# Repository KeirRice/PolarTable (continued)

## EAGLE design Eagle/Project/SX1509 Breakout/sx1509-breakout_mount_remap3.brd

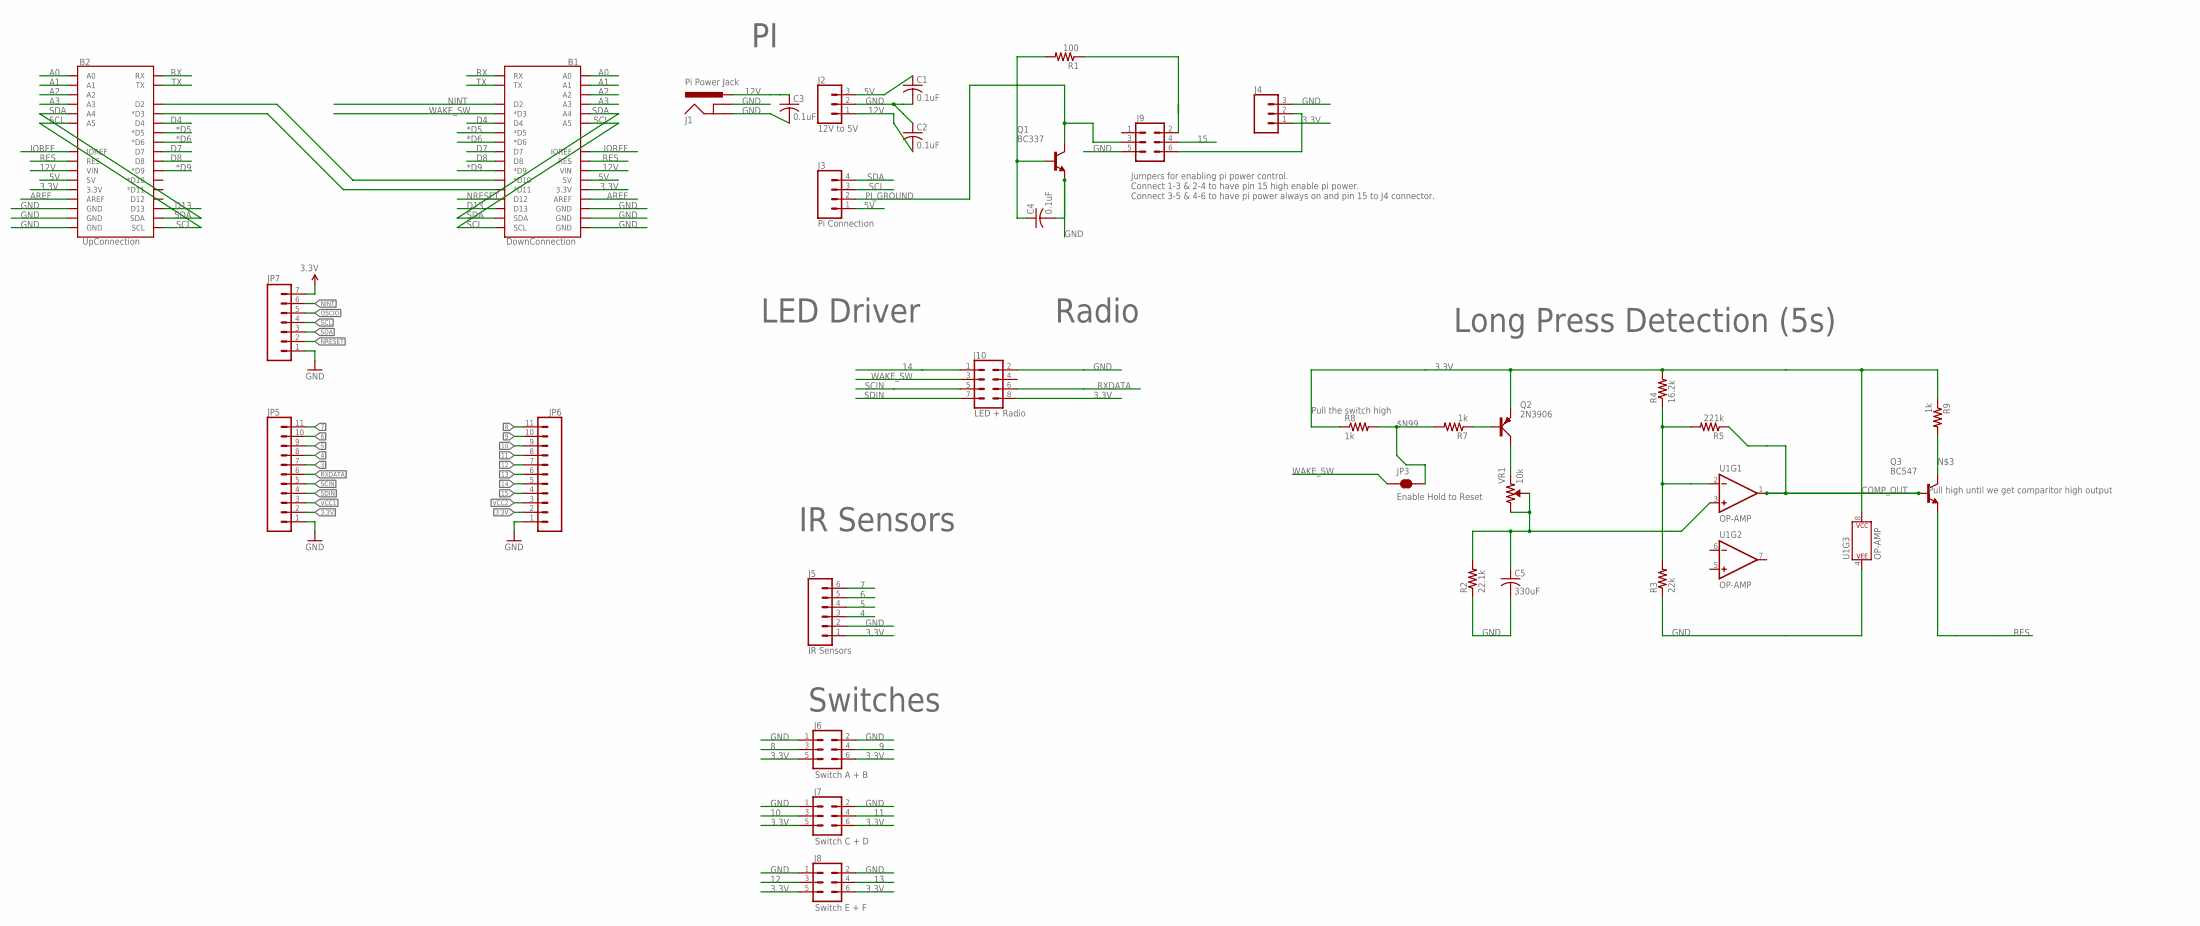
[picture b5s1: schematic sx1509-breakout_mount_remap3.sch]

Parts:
B1: DownConnection; UNO_R3_SHIELD_NOLABELS
B2: UpConnection; UNO_R3_SHIELD_NOLABELS
C1, C2, C3, C4: 0.1uF; C0805
C5: 330uF; C0805
J1: Pi Power Jack; POWER_JACK_PTH_BREAD
J2: 12V to 5V; 1X03
J3: Pi Connection; 1X04
J4: CONN_03; 1X03
J5: IR Sensors; 1X06
J6: Switch A + B; 2X3
J7: Switch C + D; 2X3
J8: Switch E + F; 2X3
J9: CONN_03X2NO_SILK; 2X3-NS
J10: LED + Radio; 2X4
JP3: Enable Hold to Reset; SMT-JUMPER_2_NC_TRACE_SILK
JP5, JP6: CONN_11; 1X11
JP7: M07; 1X07
Q1: BC337; TO92
Q2: 2N3906; TO92D
Q3: BC547; TO92
R1: 100; R0805
R2: 22.1k; R0805
R3: 22k; R0805
R4: 16.2k; R0805
R5: 221k; R0805
R7, R8, R9: 1k; R0805
U1: OP-AMP; SO08
VR1: 10k; TRIMPOT-PTH-3386U

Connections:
3: JP5.7
3.3V: B1.3.3V, B2.3.3V, J4.1, J5.1, J6.5, J6.6, J7.5, J7.6, J8.5, J8.6, J10.8, JP5.2, JP6.2, JP7.7, Q2.E, R4.2, R8.1, R9.1, U1.8 (P$V+)
4: J5.3, JP5.8
5: J5.4, JP5.9
5V: B1.5V, B2.5V, C1.1, J2.3, J3.1
6: J5.5, JP5.10
7: J5.6, JP5.11
8: J6.3, JP6.11
9: J6.4, JP6.10
10: J7.3, JP6.9
10_TO_2: B1.D10 (*D10), B2.D2
11: J7.4, JP6.8
11_TO_3: B1.D11 (*D11), B2.D3 (*D3)
12: J8.3, JP6.7
12V: B1.VIN, B2.VIN, C2.2, C3.1, J1.PWR, J2.1
13: J8.4, JP6.6
14: J10.1, JP6.5
15: J9.4, JP6.4
15_PLUG: J4.2, J9.6
$N99: JP3.2, R7.2, R8.2
*D5: B1.D5 (*D5), B2.D5 (*D5)
*D6: B1.D6 (*D6), B2.D6 (*D6)
*D9: B1.D9 (*D9), B2.D9 (*D9)
A0: B1.A0, B2.A0
A1: B1.A1, B2.A1
A2: B1.A2, B2.A2
A3: B1.A3, B2.A3
AREF: B1.AREF, B2.AREF
COMP_OUT: Q3.2 (B), R5.1, U1.1 (OUT)
D4: B1.D4, B2.D4
D7: B1.D7, B2.D7
D8: B1.D8, B2.D8
D13: B1.D13, B2.D13
GND: B1.GND@0 (GND), B1.GND@1 (GND), B1.GND@2 (GND), B2.GND@0 (GND), B2.GND@1 (GND), B2.GND@2 (GND), C1.2, C2.1, C3.2, C4.2, C5.2, J1.GND, J1.GNDBREAK, J2.2, J4.3, J5.2, J6.1, J6.2, J7.1, J7.2, J8.1, J8.2, J9.5, J10.2, JP5.1, JP6.1, JP7.1, Q1.1 (E), R2.1, R3.1, U1.4 (P$V-)
IOREF: B1.IOREF, B2.IOREF
unnamed: Q2.B, R7.1
unnamed: C4.1, Q1.2 (B), R1.2
unnamed: Q3.3 (C), R9.2
unnamed: J9.2, R1.1
unnamed: R3.2, R4.1, R5.2, U1.2 (-IN)
unnamed: Q2.C, VR1.1 (CCW)
unnamed: C5.1, R2.2, U1.3 (+IN), VR1.2 (WIPER), VR1.3 (CW)
NINT: B1.D2, JP7.6
NRESET: B1.D12, JP7.2
OSCIO: JP7.5
PI_GROUND: J3.2, J9.3, Q1.3 (C)
RES: B1.RES, B2.RES, Q3.1 (E)
RX: B1.RX, B2.RX
RXDATA: J10.6, JP5.6
SCIN: J10.5, JP5.5
SCL: B1.A5, B1.SCL, B2.A5, B2.SCL, J3.3, JP7.4
SDA: B1.A4, B1.SDA, B2.A4, B2.SDA, J3.4, JP7.3
SDIN: J10.7, JP5.4
TX: B1.TX, B2.TX
VCC1: JP5.3
VCC2: JP6.3
WAKE_SW: B1.D3 (*D3), J10.3, JP3.1

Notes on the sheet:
LED Driver
IR Sensors
Switches
Radio
Long Press Detection (5s)
Jumpers for enabling pi power control. Connect 1-3 & 2-4 to have pin 15 high enable pi power. Connect 3-5 & 4-6 to have pi power always on and pin 15 to J4 connector.

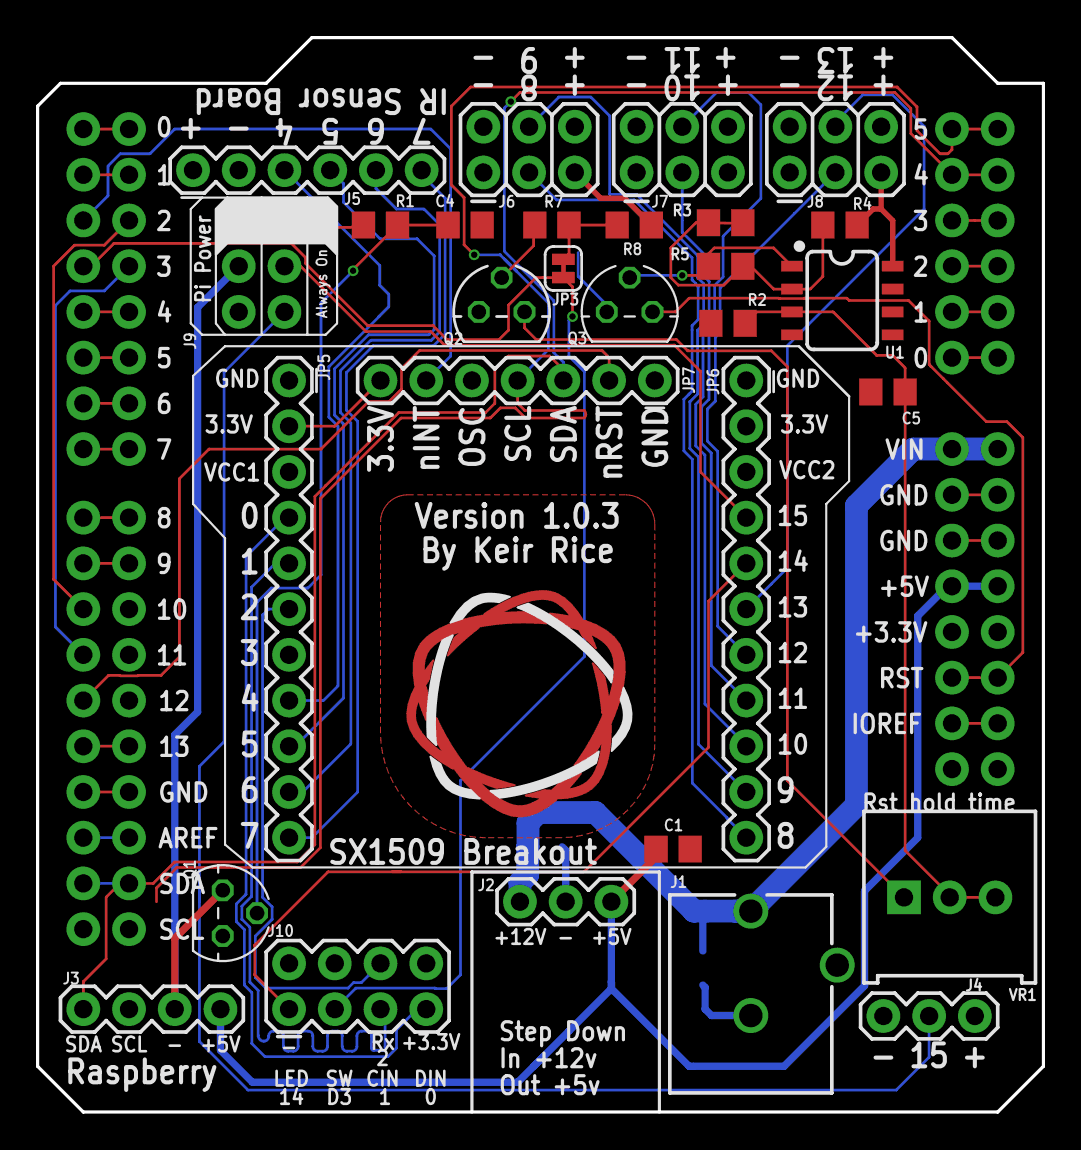
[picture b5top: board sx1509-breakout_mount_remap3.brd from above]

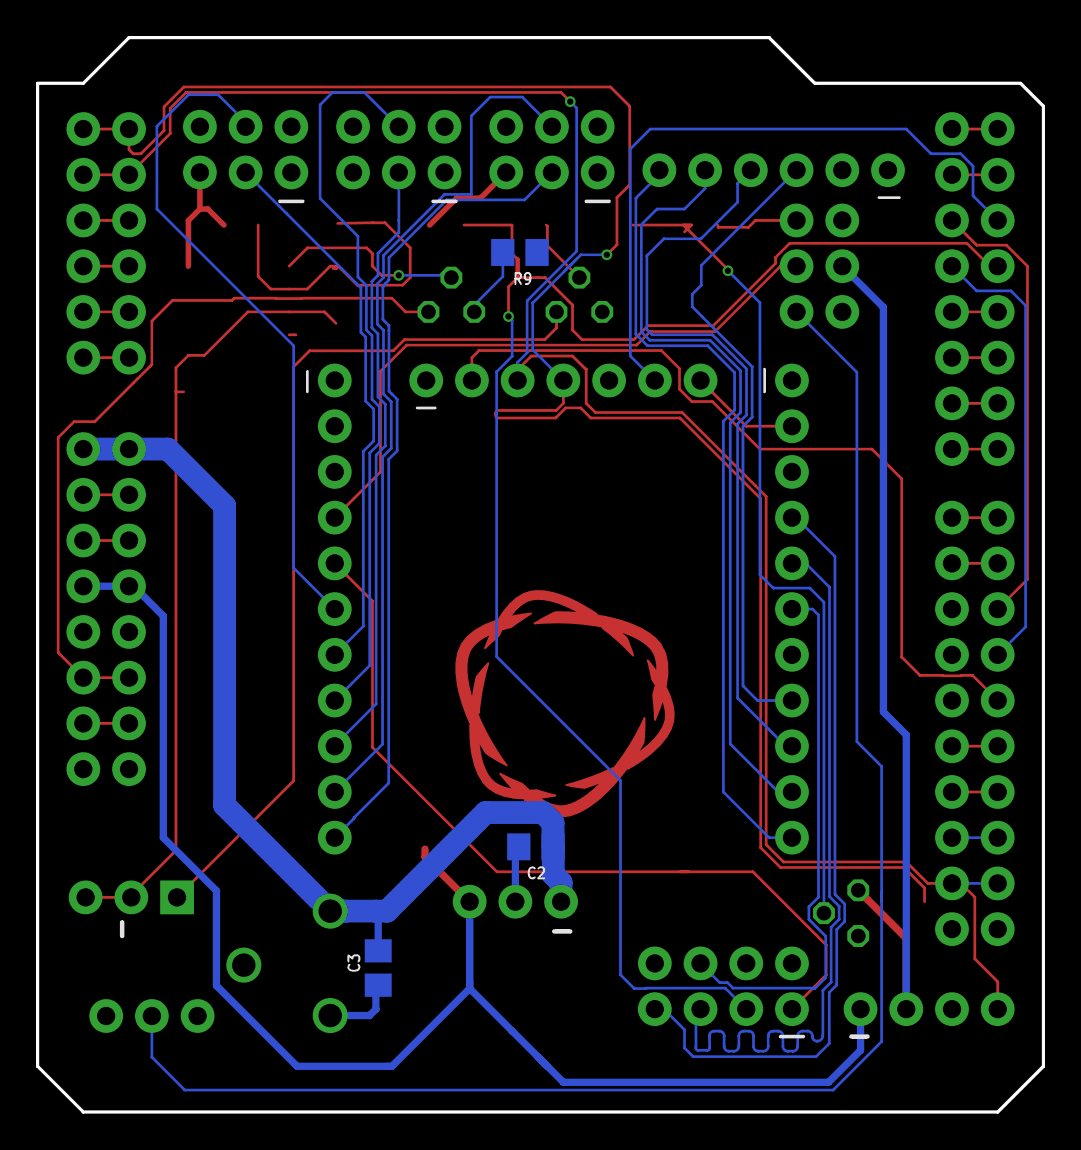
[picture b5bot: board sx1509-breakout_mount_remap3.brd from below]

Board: 2 copper layers, 55.9 x 59.7 mm, 35 parts (3 on the bottom side), 53 nets.

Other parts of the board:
U$2: TRI_LOGO_TOP_15MM

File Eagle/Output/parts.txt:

Partlist

Exported from sx1509-breakout_mount_remap5.sch at 9/27/2018 1:54 PM

EAGLE Version 9.1.3 Copyright (c) 1988-2018 Autodesk, Inc.

Assembly variant: 

Part     Value                         Device                         Package                      Library                 Sheet

B1       Connect down to Arduino       ARDUINO_UNO_R3_SHIELDNOLABELS  UNO_R3_SHIELD_NOLABELS       keir_library            1
B2       Connect up to motor shield    ARDUINO_UNO_R3_SHIELDNOLABELS  UNO_R3_SHIELD_NOLABELS       keir_library            1
C1       100u                          CPOL-EUE2-5                    E2-5                         rcl                     1
C2       100u                          CPOL-EUE2-5                    E2-5                         rcl                     1
C4       100nF                         C-EUC0805                      C0805                        resistor                1
C5       330uF                         C-EUC0805                      C0805                        resistor                1
C9       100n                          C-EUC0805                      C0805                        rcl                     1
D1       1N5408                        1N5408                         DO15-12                      keir_library            1
IC2      LM358D                        LM358D                         SO08                         keir_library            1
J1       Pi Power Jack                 POWER_JACKPTH_BREAD            POWER_JACK_PTH_BREAD         SparkFun-Connectors     1
J2       Header - Right angled, female CONN_031X03_2.54MM_RA_FEMALE   1X03                         keir_library            1
J3       Pi Connection                 CONN_041X04_1.24MM_RA_MALE     1X04_1.24MM_RA_MALE          keir_library            1
J4                                     CONN_041X04_1.24MM_RA_MALE     1X04_1.24MM_RA_MALE          keir_library            1
J5       IR Sensors                    CONN_06SILK_FEMALE_PTH         1X06                         SparkFun-Connectors     1
J6       Switch A + B                  CONN_03X22X03_2.54MM_RA_MALE   2X3                          keir_library            1
J7       Switch C + D                  CONN_03X22X03_2.54MM_RA_MALE   2X3                          keir_library            1
J8       Switch E + F                  CONN_03X22X03_2.54MM_RA_MALE   2X3                          keir_library            1
J10      LED + Radio                   CONN_04X22X4_1.24MM_RA_MALE    2X4                          keir_library            1
JP2      Bypass Power Control          JUMPER-SMT_2_NO_SILK_ROUND     SMT-JUMPER_2_NO_SILK_ROUND   SparkFun-Jumpers        1
JP3      Enable Hold to Reset          JUMPER-SMT_2_NC_TRACE_SILK     SMT-JUMPER_2_NC_TRACE_SILK   SparkFun-Jumpers        1
JP4      Route 15 to external          JUMPER-SMT_3_1-NC_TRACE_SILK   SMT-JUMPER_3_1-NC_TRACE_SILK SparkFun-Jumpers        1
JP5                                    CONN_11                        1X11                         SparkFun-Connectors     1
JP6                                    CONN_11                        1X11                         SparkFun-Connectors     1
JP7                                    M07                            1X07                         SparkFun-Connectors     1
Q1       BC337                         BC337                          TO92                         transistor-npn          1
Q2       2N3906                        2N3906                         TO92D                        transistor-small-signal 1
Q3       BC547                         BC547                          TO92                         transistor-npn          1
R1       100                           R-US_R0805                     R0805                        resistor                1
R2       22.1k                         R-US_R0805                     R0805                        resistor                1
R3       22k                           R-US_R0805                     R0805                        resistor                1
R4       16.2k                         R-US_R0805                     R0805                        resistor                1
R5       221k                          R-US_R0805                     R0805                        resistor                1
R7       1k                            R-US_R0805                     R0805                        resistor                1
R8       1k                            R-US_R0805                     R0805                        resistor                1
R9       1k                            R-US_R0805                     R0805                        resistor                1
U3       SN74HC595DR                   SN74HC595HCD                   SO16                         keir_library            1
VR1      10k                           TRIMPOT-PTH-10MM-KNOB-1/2W-10% TRIMPOT-PTH-3386U            SparkFun-Resistors      1

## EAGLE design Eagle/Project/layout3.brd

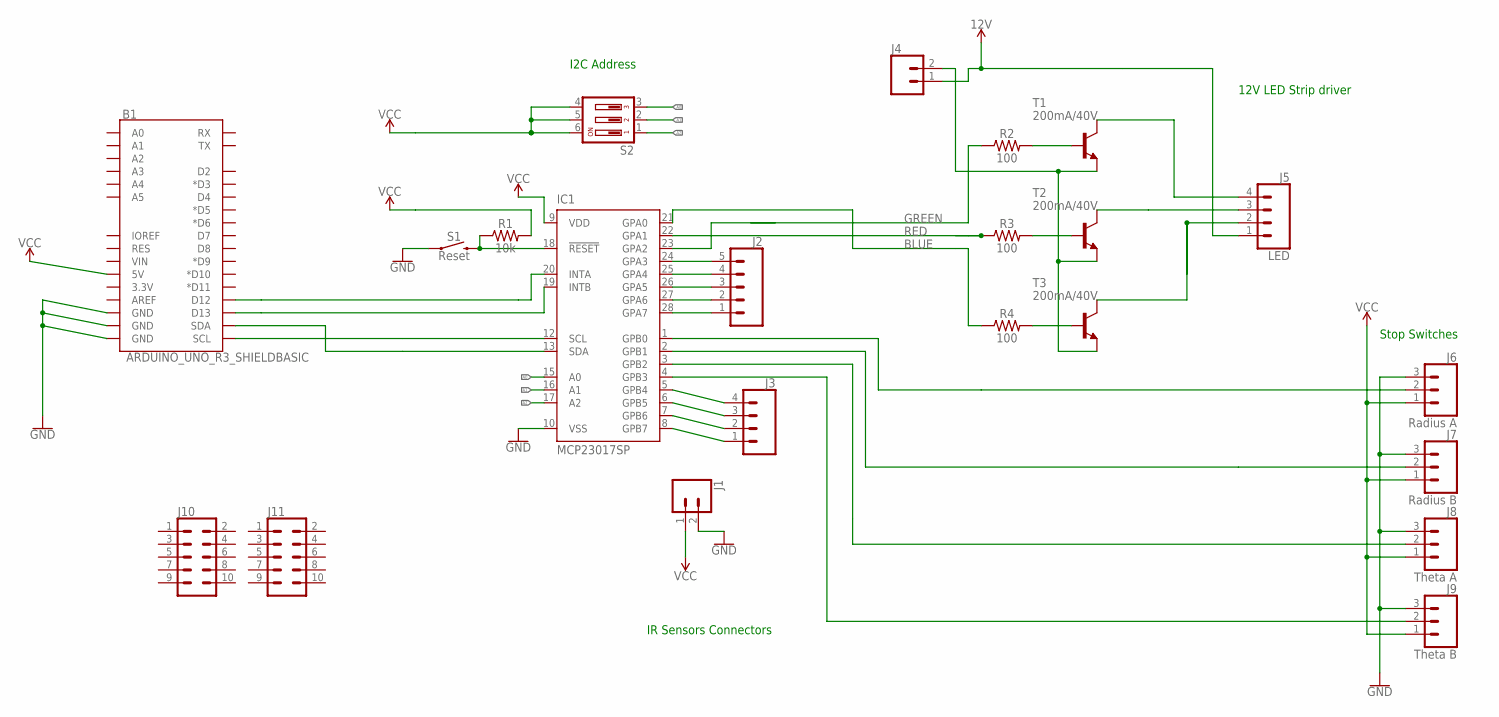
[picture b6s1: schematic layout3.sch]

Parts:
B1: ARDUINO_UNO_R3_SHIELDBASIC; UNO_R3_SHIELD
IC1: MCP23017SP; DIL28-3
J1: CONN_02POLAR; MOLEX-1X2
J2: CONN_05; 1X05
J3: CONN_041.27MM; 1X04_1.27MM
J4: CONN_023.5MM; SCREWTERMINAL-3.5MM-2
J5: LED; MOLEX-1X4
J6: Radius A; MOLEX-1X3
J7: Radius B; MOLEX-1X3
J8: Theta A; MOLEX-1X3
J9: Theta B; MOLEX-1X3
J10, J11: CONN_05X2NO_SILK; 2X5_NOSILK
R1: 10k; 0603
R2, R3, R4: 100; 0603
S1: Reset; TACTILE_SWITCH_PTH_6.0MM
S2: DS03; DS-03
T1, T2, T3: 200mA/40V; TO220

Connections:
12V: J4.1, J5.1
A0: IC1.15 (A0), S2.3
A1: IC1.16 (A1), S2.2
A2: IC1.17 (A2), S2.1
BLUE: IC1.21 (GPA0), R4.1
GND: B1.GND@0 (GND), B1.GND@1 (GND), B1.GND@2 (GND), IC1.10 (VSS), J1.2, J6.3, J7.3, J8.3, J9.3, S1.1
GREEN: IC1.23 (GPA2), R2.1
INT_A: B1.D12, IC1.20 (INTA)
INT_B: B1.D13, IC1.19 (INTB)
IR_A: IC1.5 (GPB4), J3.4
IR_B: IC1.6 (GPB5), J3.3
IR_C: IC1.7 (GPB6), J3.2
IR_D: IC1.8 (GPB7), J3.1
unnamed: R2.2, T1.1 (B)
unnamed: J5.4, T1.2 (C)
unnamed: R3.2, T2.1 (B)
unnamed: J5.3, T2.2 (C)
unnamed: R4.2, T3.1 (B)
unnamed: J5.2, T3.2 (C)
unnamed: J4.2, T1.3 (E), T2.3 (E), T3.3 (E)
unnamed: IC1.28 (GPA7), J2.1
unnamed: IC1.27 (GPA6), J2.2
unnamed: IC1.26 (GPA5), J2.3
unnamed: IC1.25 (GPA4), J2.4
unnamed: IC1.24 (GPA3), J2.5
RADIUS_A: IC1.1 (GPB0), J6.2
RADIUS_B: IC1.2 (GPB1), J7.2
RED: IC1.22 (GPA1), R3.1
RESET: IC1.18 (!RESET), R1.1, S1.3 (2)
SDA: B1.SDA, IC1.13 (SDA)
SDL: B1.SCL, IC1.12 (SCL)
THETA_A: IC1.3 (GPB2), J8.2
THETA_B: IC1.4 (GPB3), J9.2
VCC: B1.5V, IC1.9 (VDD), J1.1, J6.1, J7.1, J8.1, J9.1, R1.2, S2.4, S2.5, S2.6

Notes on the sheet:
Stop Switches
12V LED Strip driver
I2C Address
IR Sensors Connectors

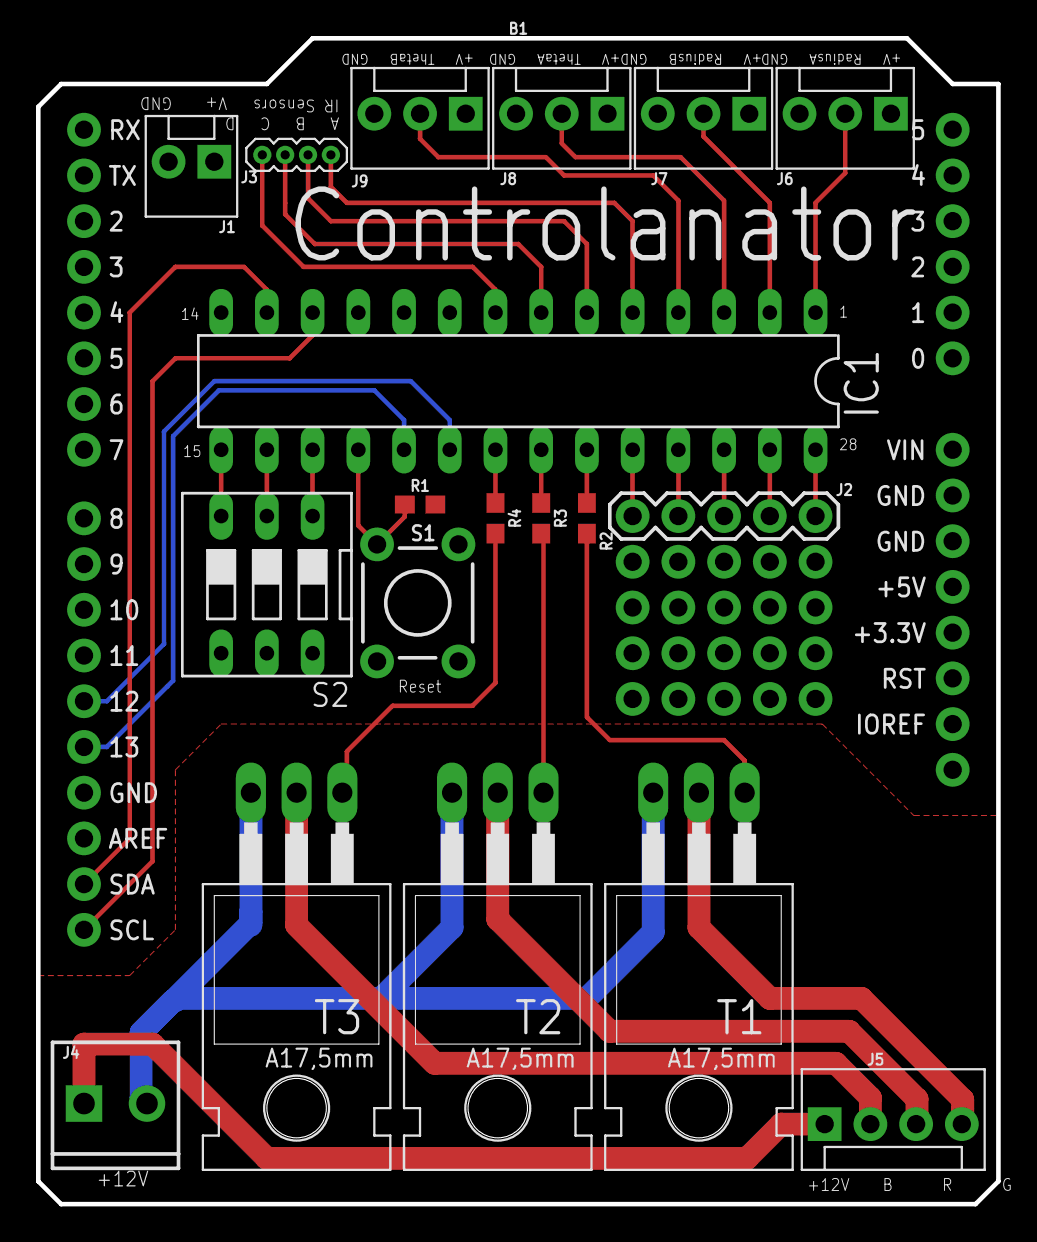
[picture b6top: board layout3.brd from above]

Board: 2 copper layers, 53.3 x 64.8 mm, 22 parts (0 on the bottom side), 34 nets.

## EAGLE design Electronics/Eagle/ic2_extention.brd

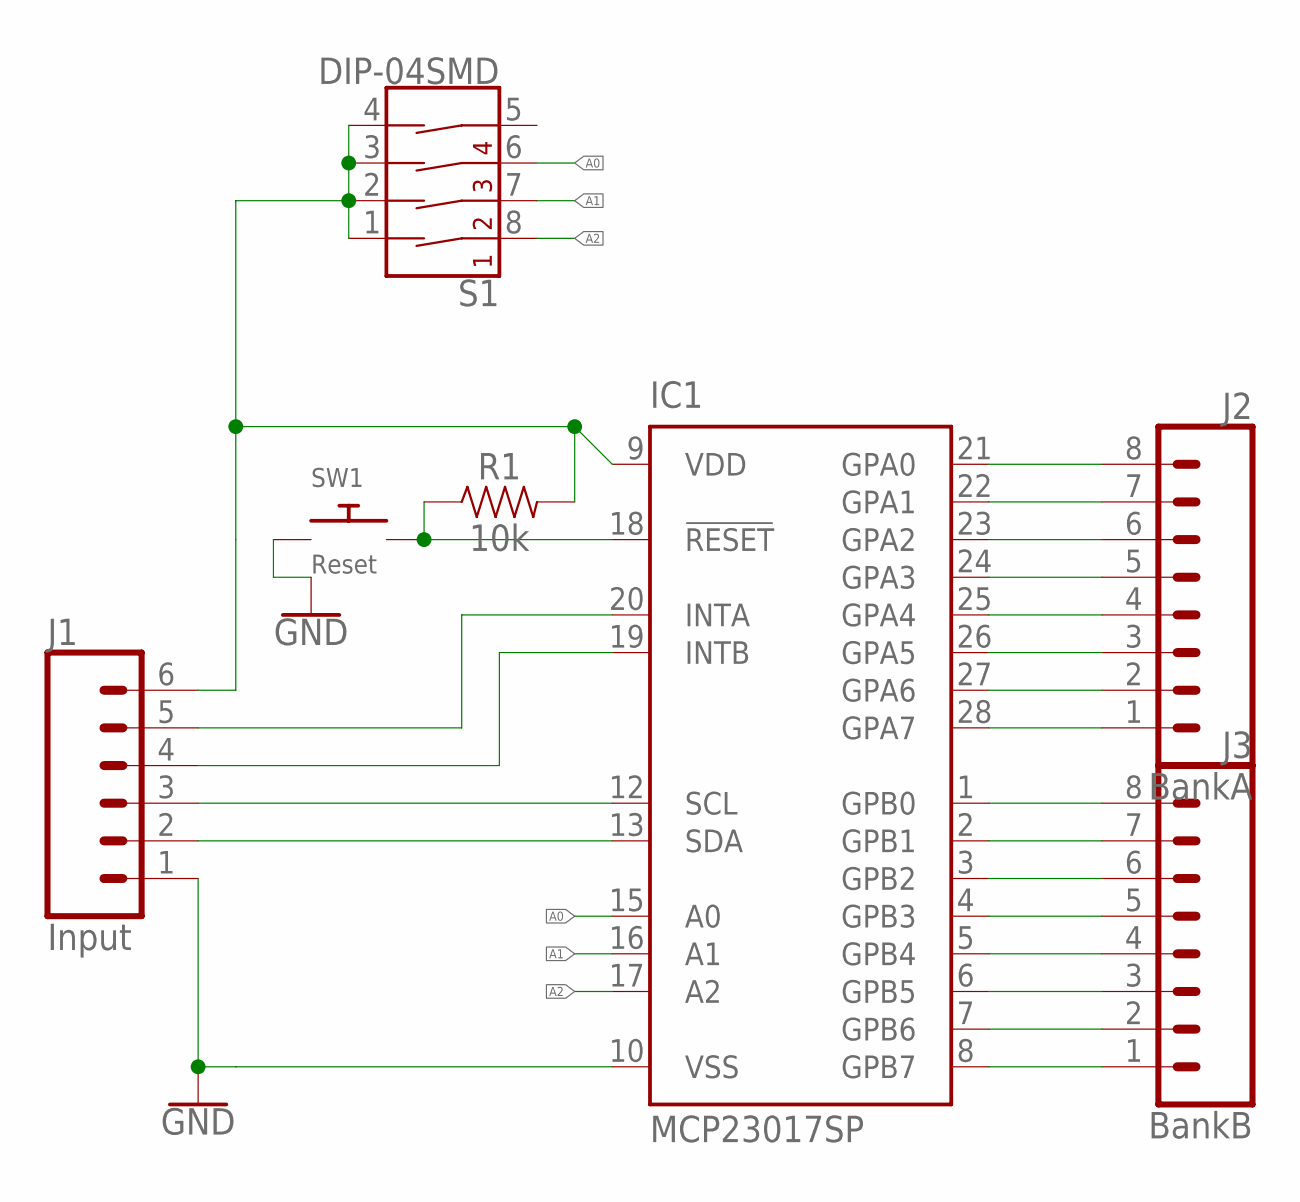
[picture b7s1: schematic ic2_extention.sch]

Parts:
IC1: MCP23017SP; DIL28-3
J1: Input; 1X06_LOCK
J2: BankA; 1X08
J3: BankB; 1X08
R1: 10k; 0603
S1: DIP-04SMD; DIPSWITCH-04-SMD
SW1: Reset; BTN_CK_KSS

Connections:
A0: IC1.15 (A0), S1.6 (3B)
A1: IC1.16 (A1), S1.7 (2B)
A2: IC1.17 (A2), S1.8 (1B)
GND: IC1.10 (VSS), J1.1, SW1.P$1
unnamed: IC1.18 (!RESET), R1.1, SW1.P$2
unnamed: IC1.20 (INTA), J1.5
unnamed: IC1.19 (INTB), J1.4
unnamed: IC1.28 (GPA7), J2.1
unnamed: IC1.27 (GPA6), J2.2
unnamed: IC1.26 (GPA5), J2.3
unnamed: IC1.25 (GPA4), J2.4
unnamed: IC1.24 (GPA3), J2.5
unnamed: IC1.23 (GPA2), J2.6
unnamed: IC1.22 (GPA1), J2.7
unnamed: IC1.21 (GPA0), J2.8
unnamed: IC1.8 (GPB7), J3.1
unnamed: IC1.7 (GPB6), J3.2
unnamed: IC1.6 (GPB5), J3.3
unnamed: IC1.5 (GPB4), J3.4
unnamed: IC1.4 (GPB3), J3.5
unnamed: IC1.3 (GPB2), J3.6
unnamed: IC1.2 (GPB1), J3.7
unnamed: IC1.1 (GPB0), J3.8
unnamed: IC1.12 (SCL), J1.3
unnamed: IC1.13 (SDA), J1.2
VDD: IC1.9 (VDD), J1.6, R1.2, S1.1 (1A), S1.2 (2A), S1.3 (3A), S1.4 (4A)

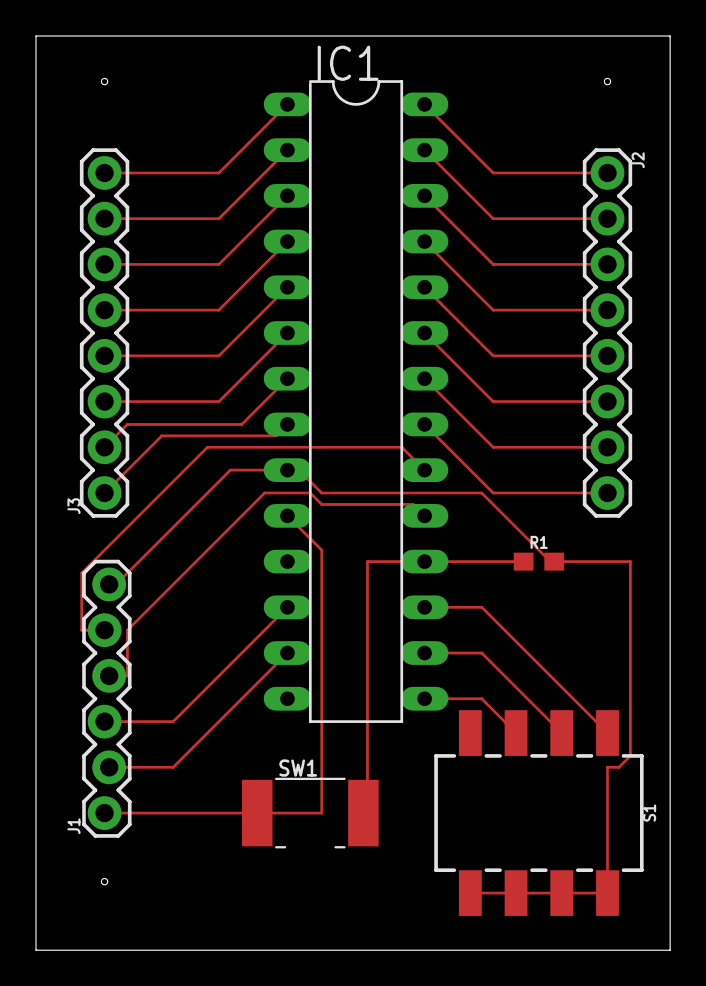
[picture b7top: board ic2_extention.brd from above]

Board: 2 copper layers, 35.2 x 50.8 mm, 7 parts (0 on the bottom side), 26 nets.

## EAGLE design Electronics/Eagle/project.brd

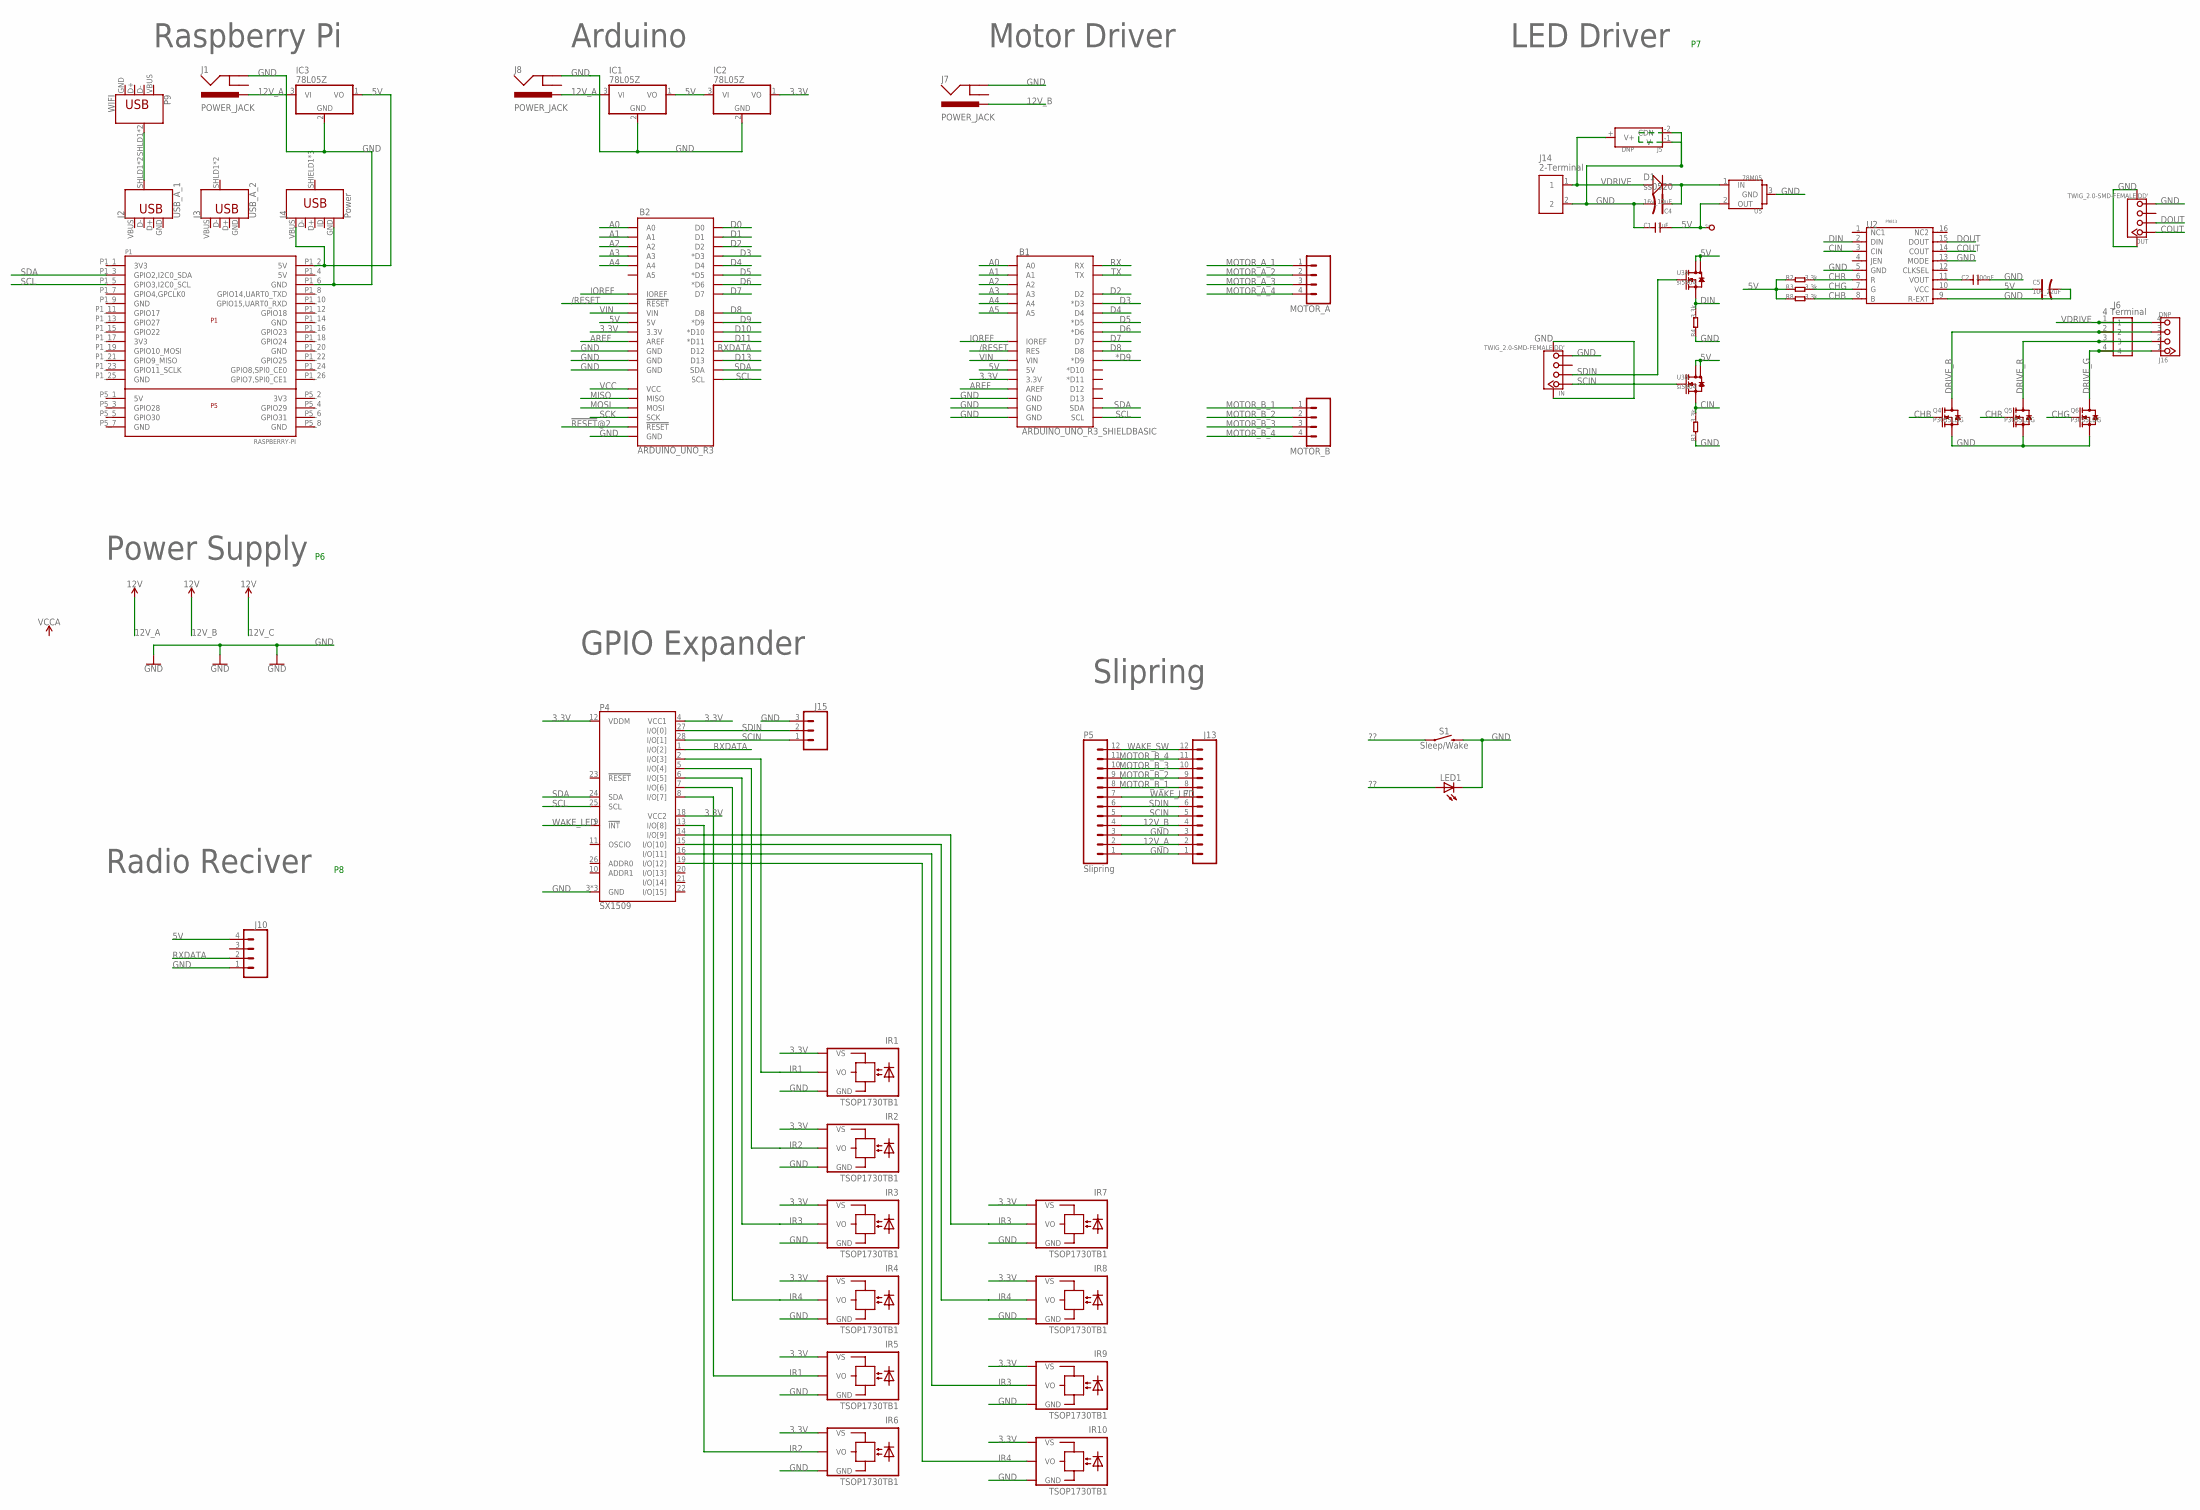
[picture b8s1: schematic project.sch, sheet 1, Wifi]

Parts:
5V: DNP; TP_3535
B1: ARDUINO_UNO_R3_SHIELDBASIC; UNO_R3_SHIELD
B2: ARDUINO_UNO_R3; ARDUINO_R3
C1: 1uF; 0805
C2: 100nF; 0402
C4: 16v_10uF; AVX-A
C5: 10v_22uF; AVX-A
D1: ss0520; SOD123
IC1, IC2, IC3: 78L05Z; TO92
IN: TWIG_2.0-SMD-FEMALE'DD'; 2.0_1X4DD
IR1, IR2, IR3, IR4, IR5, IR6, IR7, IR8, IR9, IR10: TSOP1730TB1; TSOP17_TB1
J1, J7, J8: POWER_JACK; POWER_JACK_PTH
J2: USB_A_1; USB-A-S-SILK-FEMALE
J3: USB_A_2; USB-A-S-SILK-FEMALE
J4: Power; USB-B-MICRO-SMD
J5: DNP; PW-3P-2.5
J6: 4 Terminal; 4P-2.54-15.6X12.2X13.2
J10: CONN_04; 1X04
J13: CONN_12; 1X12
J14: 2-Terminal; 2P-2.54-12.1X8.5X13.4
J15: CONN_03; 1X03
J16: DNP; 4P-2.54-90
LED1: LED5MM
MOTOR_A: CONN_04SCREW; SCREWTERMINAL-3.5MM-4
MOTOR_B: CONN_04SCREW; SCREWTERMINAL-3.5MM-4
OUT: TWIG_2.0-SMD-FEMALE'DD'; 2.0_1X4DD
P1: RASPBERRY-PI; RASPBERRY-PI_REV2
P4: SX1509; QFN-28
P5: Slipring; 1X12
P9: WIFI; USB-A-H
Q4, Q5, Q6: P3055LDG; TO252
R1, R2, R3, R4, R8: 3.3k; 0402
S1: Sleep/Wake; TACTILE_SWITCH_PTH_6.0MM
U2: P9813; SSOP16
U3: si5904; 1206-8
U5: 78M05; TO252

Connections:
3.3V: B1.3.3V, B2.3.3V, IC2.1 (VO), IR1.VS, IR2.VS, IR3.VS, IR4.VS, IR5.VS, IR6.VS, IR7.VS, IR8.VS, IR9.VS, IR10.VS, P4.4 (VCC1), P4.12 (VDDM), P4.18 (VCC2)
5V: 5V.T, B1.5V, B2.5V, C1.2, C5.+, IC1.1 (VO), IC2.3 (VI), IC3.1 (VO), J4.VBUS, J10.4, P1.P1_2 (5V), R2.1, R3.1, R8.1, U2.10 (VCC), U3.5 (D), U3.6 (D), U3.7 (D), U3.8 (D), U5.2 (OUT)
12V_A: IC1.3 (VI), IC3.3 (VI), J1.PWR, J8.PWR, J13.2, P5.2
12V_B: J7.PWR, J13.4, P5.4
!RESET!@2: B2.RESET@2 (!RESET!)
*D9: B1.D9 (*D9)
/RESET: B1.RES, B2.RESET@1 (!RESET!)
??: LED1.A, S1.1
A0: B1.A0, B2.A0
A1: B1.A1, B2.A1
A2: B1.A2, B2.A2
A3: B1.A3, B2.A3
A4: B1.A4, B2.A4
A5: B1.A5
AREF: B1.AREF, B2.AREF
CHB: Q4.1 (G), R8.2, U2.8 (B)
CHG: Q6.1 (G), R3.2, U2.7 (G)
CHR: Q5.1 (G), R2.2, U2.6 (R)
CIN: R1.2, U2.3 (CIN), U3.3 (S)
COUT: OUT.1, U2.14 (COUT)
D0: B2.D0
D1: B2.D1
D2: B1.D2, B2.D2
D3: B1.D3 (*D3), B2.D3 (*D3)
D4: B1.D4, B2.D4
D5: B1.D5 (*D5), B2.D5 (*D5)
D6: B1.D6 (*D6), B2.D6 (*D6)
D7: B1.D7, B2.D7
D8: B1.D8, B2.D8
D9: B2.D9 (*D9)
D10: B2.D10 (*D10)
D11: B2.D11 (*D11)
D13: B2.D13
DIN: R4.2, U2.2 (DIN), U3.1 (S)
DOUT: OUT.2, U2.15 (DOUT)
DRIVE_B: J6.2, J16.3, Q4.2 (D)
DRIVE_G: J6.4, J16.1, Q6.2 (D)
DRIVE_R: J6.3, J16.2, Q5.2 (D)
GND: B1.GND@0 (GND), B1.GND@1 (GND), B1.GND@2 (GND), B2.GND@1 (GND), B2.GND@2 (GND), B2.GND@3 (GND), B2.GND@4 (GND), C1.1, C2.2, C4.-, C5.-, IC1.2 (GND), IC2.2 (GND), IC3.2 (GND), IN.4, IN.SS1, IN.SS2, IR1.GND, IR2.GND, IR3.GND, IR4.GND, IR5.GND, IR6.GND, IR7.GND, IR8.GND, IR9.GND, IR10.GND, J1.GND, J2.GND, J3.GND, J4.GND, J5.-1 (V-), J5.-2 (CDN), J7.GND, J8.GND, J10.1, J13.1, J13.3, J14.2, J15.3, LED1.K (C), OUT.4, OUT.SS1, OUT.SS2, P1.P1_6 (GND), P4.3 (GND), P4.17 (GND), P4.29 (GND), P5.1, P5.3, P9.GND, Q4.3 (S), Q5.3 (S), Q6.3 (S), R1.1, R4.1, S1.3 (2), U2.5 (GND), U2.9 (R-EXT), U2.13 (MODE), U5.3 (GND)
IOREF: B1.IOREF, B2.IOREF
IR1: IR1.VO, IR5.VO, P4.2 (I/O[3]), P4.8 (I/O[7])
IR2: IR2.VO, IR6.VO, P4.5 (I/O[4]), P4.13 (I/O[8])
IR3: IR3.VO, IR7.VO, IR9.VO, P4.6 (I/O[5]), P4.14 (I/O[9]), P4.16 (I/O[11])
IR4: IR4.VO, IR8.VO, IR10.VO, P4.7 (I/O[6]), P4.15 (I/O[10]), P4.19 (I/O[12])
MISO: B2.MISO
MOSI: B2.MOSI
MOTOR_A_1: MOTOR_A.1
MOTOR_A_2: MOTOR_A.2
MOTOR_A_3: MOTOR_A.3
MOTOR_A_4: MOTOR_A.4
MOTOR_B_1: J13.8, MOTOR_B.1, P5.8
MOTOR_B_2: J13.9, MOTOR_B.2, P5.9
MOTOR_B_3: J13.10, MOTOR_B.3, P5.10
MOTOR_B_4: J13.11, MOTOR_B.4, P5.11
unnamed: J2.SHLD1 (SHIELD), J2.SHLD2 (SHIELD), P9.SHLD1 (SHIELD), P9.SHLD2 (SHIELD)
unnamed: C2.1, U2.11 (VOUT)
unnamed: C4.+, D1.-, U5.1 (IN)
RX: B1.RX
RXDATA: B2.D12, J10.2, P4.1 (I/O[2])
SCIN: IN.1, J13.5, J15.1, P4.28 (I/O[1]), P5.5, U3.4 (G)
SCK: B2.SCK
SCL: B1.SCL, B2.SCL, P1.P1_5 (GPIO3,I2C0_SCL), P4.25 (SCL)
SDA: B1.SDA, B2.SDA, P1.P1_3 (GPIO2,I2C0_SDA), P4.24 (SDA)
SDIN: IN.2, J13.6, J15.2, P4.27 (I/O[0]), P5.6, U3.2 (G)
TX: B1.TX
VBUS: J2.VBUS, J3.VBUS, P9.VBUS
VCC: B2.VCC
VDRIVE: D1.+, J5.+ (V+), J6.1, J14.1, J16.4
VIN: B1.VIN, B2.VIN
WAKE_LED: J13.7, P4.9 (!INT), P5.7
WAKE_SW: J13.12, P5.12

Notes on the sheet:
Arduino
Motor Driver
Power Supply
Raspberry Pi
LED Driver
GPIO Expander
Slipring
Radio Reciver

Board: 2 copper layers, 55 parts (0 on the bottom side), 52 nets, no tracks yet.
